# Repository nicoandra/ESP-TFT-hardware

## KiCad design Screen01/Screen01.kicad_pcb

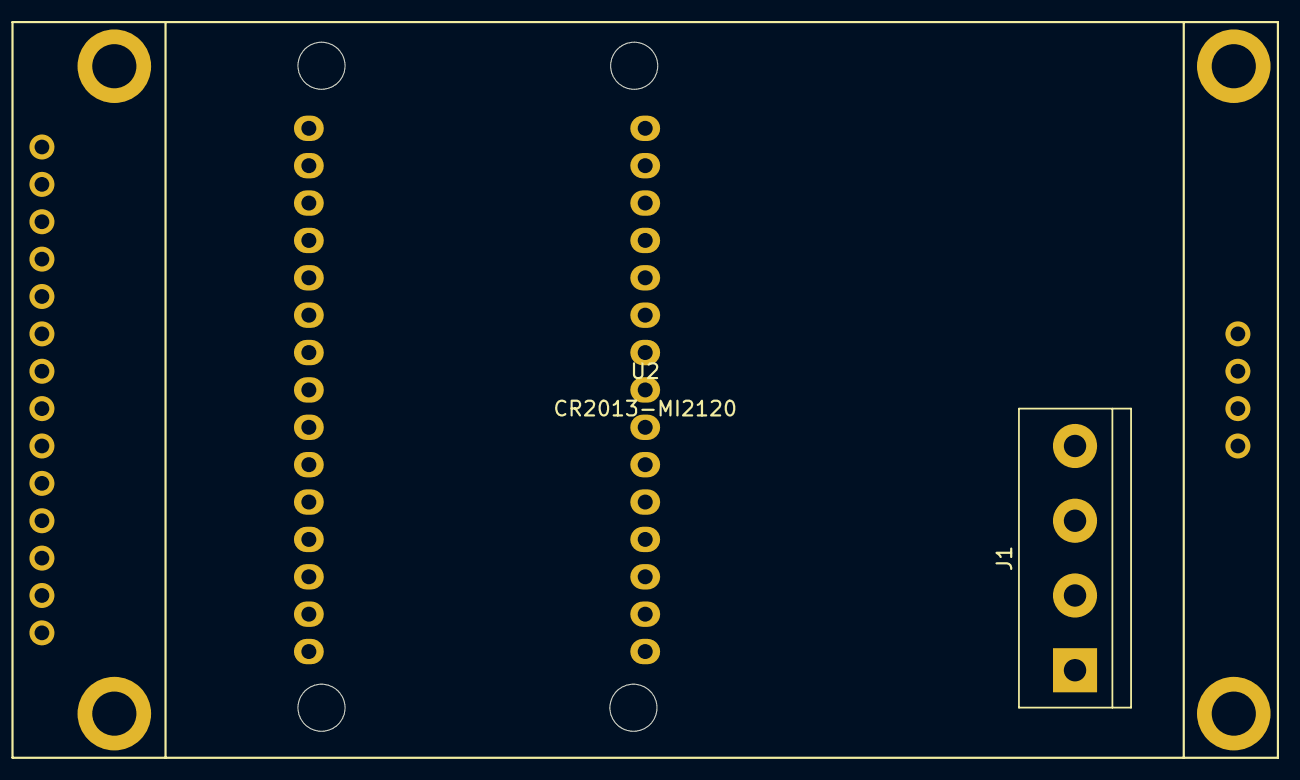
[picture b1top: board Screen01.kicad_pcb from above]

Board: 2 copper layers, 3 parts (1 on the bottom side), 12 nets, no tracks yet.

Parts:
J1: UlrSonc; TerminalBlock_bornier-4_P5.08mm
U1: NodeMCU; NodeMCU_Amica_R2
U2: CR2013-MI2120; TJCTM24028-SPI

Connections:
+5V: J1.1, U1.15
/3V: U1.16, U2.1, U2.4, U2.8
/CS: U1.20, U2.3
/DC: U1.26, U2.5
/ECHO: J1.3, U1.27
/SCK: U1.23, U2.7, U2.10
/SDI: U1.21, U2.6, U2.12
/SDO: U1.22, U2.9, U2.13
/TCS: U1.28, U2.11
/TIRQ: U1.29, U2.14
/TRIG: J1.2, U1.30
GND: J1.4, U1.10, U1.14, U1.17, U1.24, U2.2

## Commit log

2018-12-02 First commit, setting libraries up
2018-12-02 PCB and Mappings
2018-12-04 Will use an ultrasonic sensor instead of a PIR
